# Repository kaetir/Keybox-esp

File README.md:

# Keybox-esp
Nouvelle version de la keybox avec un esp32

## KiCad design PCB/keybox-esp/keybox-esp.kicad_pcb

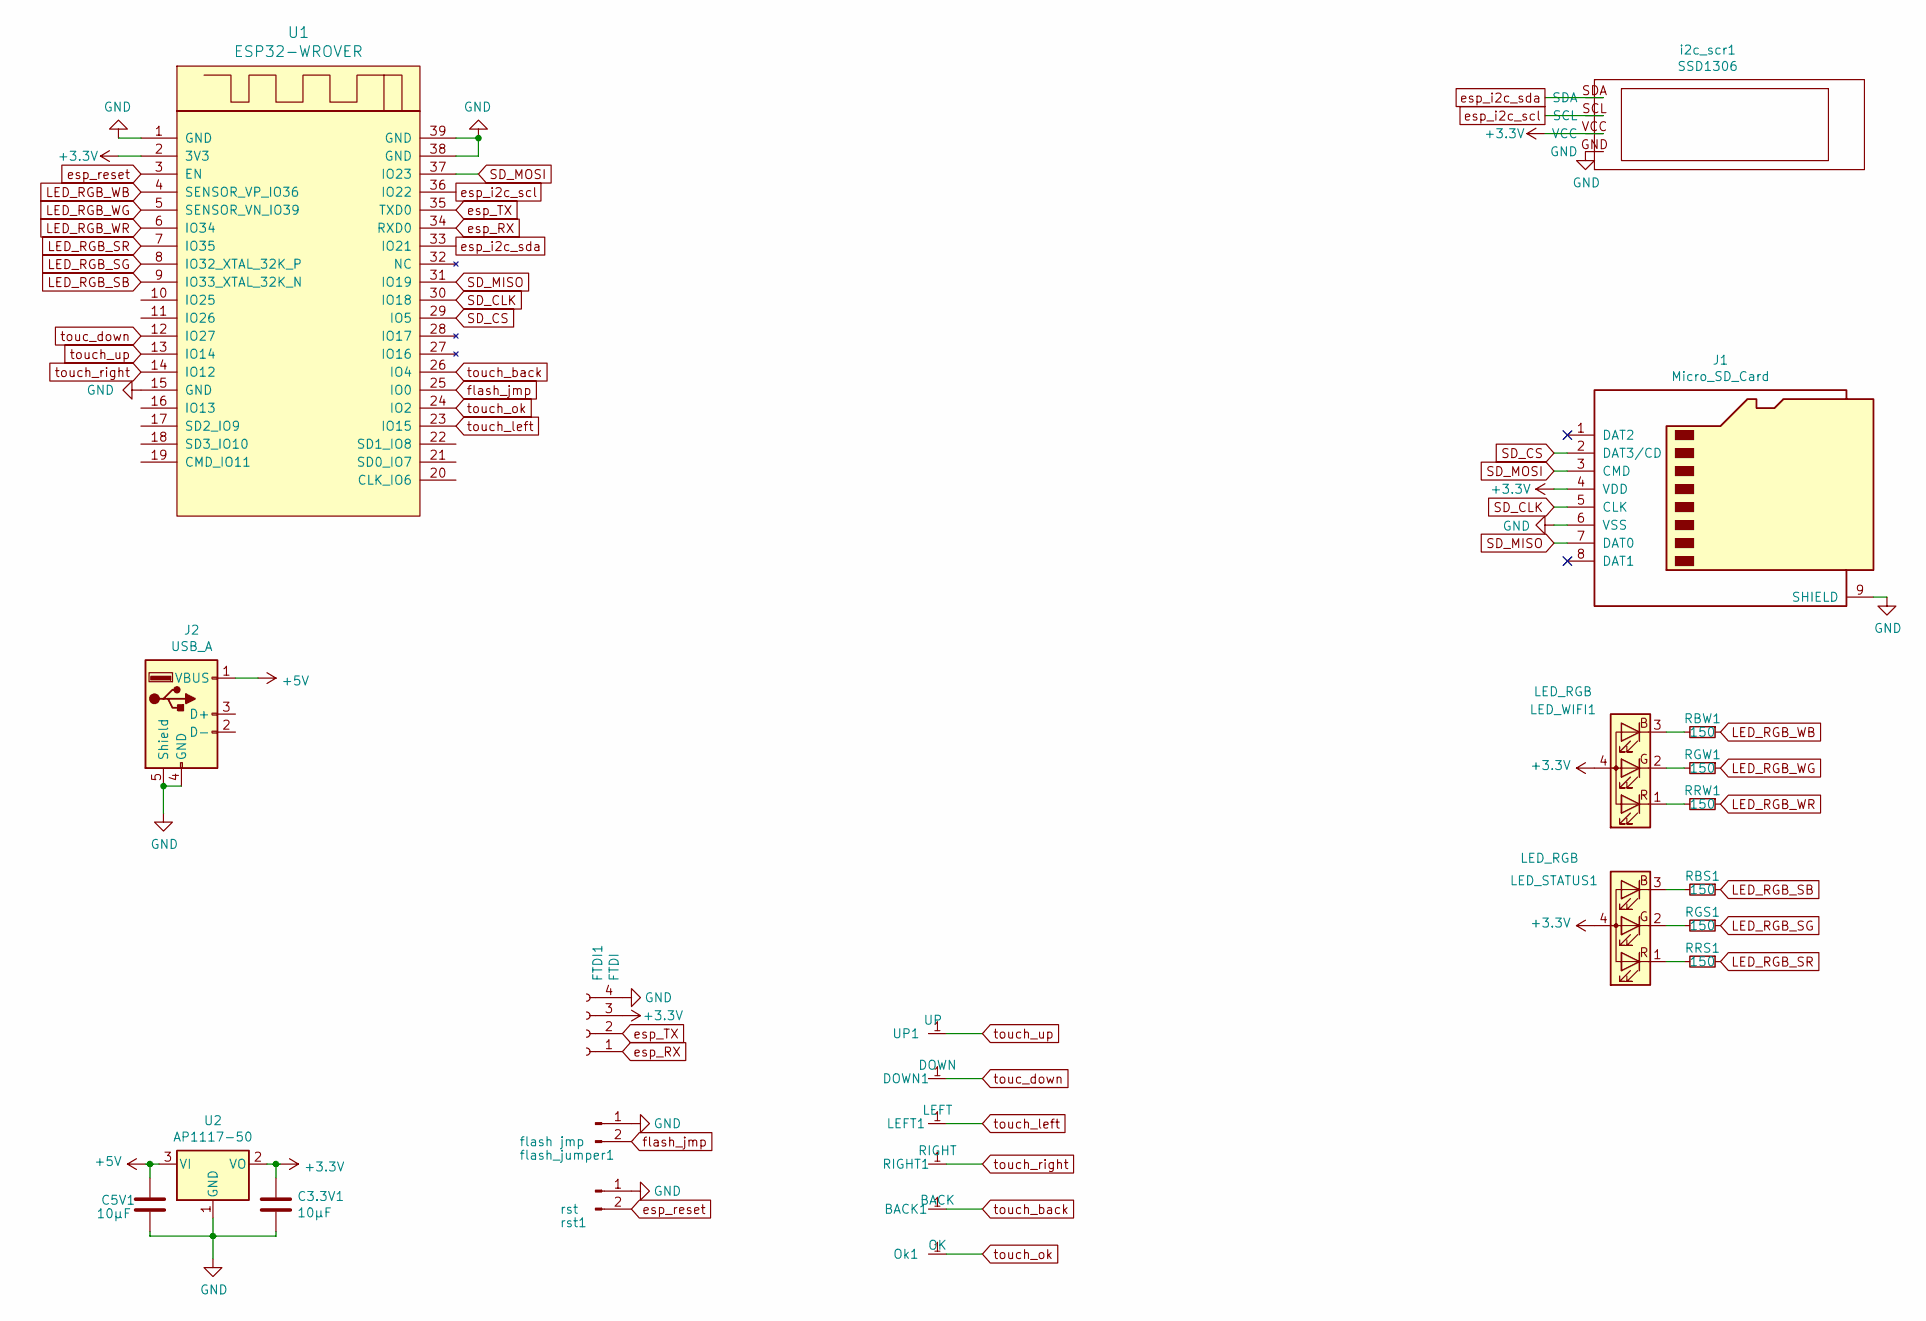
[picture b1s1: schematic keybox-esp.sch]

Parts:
BACK1: BACK; simple_pad_solder
C3.3V1, C5V1: 10µF; C_1206_3216Metric
DOWN1: DOWN; simple_pad_solder
FTDI1: FTDI; SolderWirePad_1x04_P3.175mm_Drill0.8mm
J1: Micro_SD_Card; microSD_HC_Hirose_DM3AT-SF-PEJM5
J2: USB_A; USB3_A_Plug_Wuerth_692112030100_Horizontal
LED_STATUS1: LED_RGB; LED_Avago_PLCC4_3.2x2.8mm_CW
LED_WIFI1: LED_RGB; LED_Avago_PLCC4_3.2x2.8mm_CW
LEFT1: LEFT; simple_pad_solder
Ok1: OK; simple_pad_solder
RBS1: 150; R_1206_3216Metric_Pad1.42x1.75mm_HandSolder
RBW1: 150; R_1206_3216Metric_Pad1.42x1.75mm_HandSolder
RGS1: 150; R_1206_3216Metric_Pad1.42x1.75mm_HandSolder
RGW1: 150; R_1206_3216Metric_Pad1.42x1.75mm_HandSolder
RIGHT1: RIGHT; simple_pad_solder
RRS1: 150; R_1206_3216Metric_Pad1.42x1.75mm_HandSolder
RRW1: 150; R_1206_3216Metric_Pad1.42x1.75mm_HandSolder
U1: ESP32-WROVER
U2: AP1117-50; SOT-223-3Lead_TabPin2
UP1: UP; simple_pad_solder
flash_jumper1: flash jmp; jumper_smd
i2c_scr1: SSD1306; i2c_screen
rst1: rst; jumper_smd

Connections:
+3V3: C3.3V1.1, FTDI1.3, J1.4 (VDD), LED_STATUS1.4 (A), LED_WIFI1.4 (A), U1.2 (3V3), U2.2 (VO), i2c_scr1.VCC; also elsewhere on the board
+5V: C5V1.1, J2.1 (VBUS), U2.3 (VI)
GND: C3.3V1.2, C5V1.2, FTDI1.4, J1.6 (VSS), J1.9 (SHIELD), J2.4 (GND), J2.5 (Shield), U1.1 (GND), U1.15 (GND), U1.38 (GND), U1.39 (GND), U2.1 (GND), flash_jumper1.1, rst1.1
LED_RGB_SB: RBS1.1, U1.9 (IO33_XTAL_32K_N)
LED_RGB_SG: RGS1.1, U1.8 (IO32_XTAL_32K_P)
LED_RGB_SR: RRS1.1, U1.7 (IO35)
LED_RGB_WB: RBW1.1, U1.4 (SENSOR_VP_IO36)
LED_RGB_WG: RGW1.1, U1.5 (SENSOR_VN_IO39)
LED_RGB_WR: RRW1.1, U1.6 (IO34)
unnamed 13: LED_STATUS1.1 (RK), RRS1.2; also elsewhere on the board
unnamed 14: LED_STATUS1.2 (GK), RGS1.2; also elsewhere on the board
unnamed 15: LED_STATUS1.3 (BK), RBS1.2; also elsewhere on the board
unnamed 16: LED_WIFI1.1 (RK), RRW1.2; also elsewhere on the board
unnamed 17: LED_WIFI1.2 (GK), RGW1.2; also elsewhere on the board
unnamed 18: LED_WIFI1.3 (BK), RBW1.2; also elsewhere on the board
SD_CLK: J1.5 (CLK), U1.30 (IO18)
SD_CS: J1.2 (DAT3/CD), U1.29 (IO5)
SD_MISO: J1.7 (DAT0), U1.31 (IO19)
SD_MOSI: J1.3 (CMD), U1.37 (IO23)
esp_RX: FTDI1.1, U1.34 (RXD0)
esp_TX: FTDI1.2, U1.35 (TXD0)
esp_i2c_scl: U1.36 (IO22), i2c_scr1.SCL
esp_i2c_sda: U1.33 (IO21), i2c_scr1.SDA
esp_reset: U1.3 (EN), rst1.2
flash_jmp: U1.25 (IO0), flash_jumper1.2
touc_down: DOWN1.1, U1.12 (IO27)
touch_back: BACK1.1, U1.26 (IO4)
touch_left: LEFT1.1, U1.23 (IO15)
touch_ok: Ok1.1, U1.24 (IO2)
touch_right: RIGHT1.1, U1.14 (IO12)
touch_up: U1.13 (IO14), UP1.1

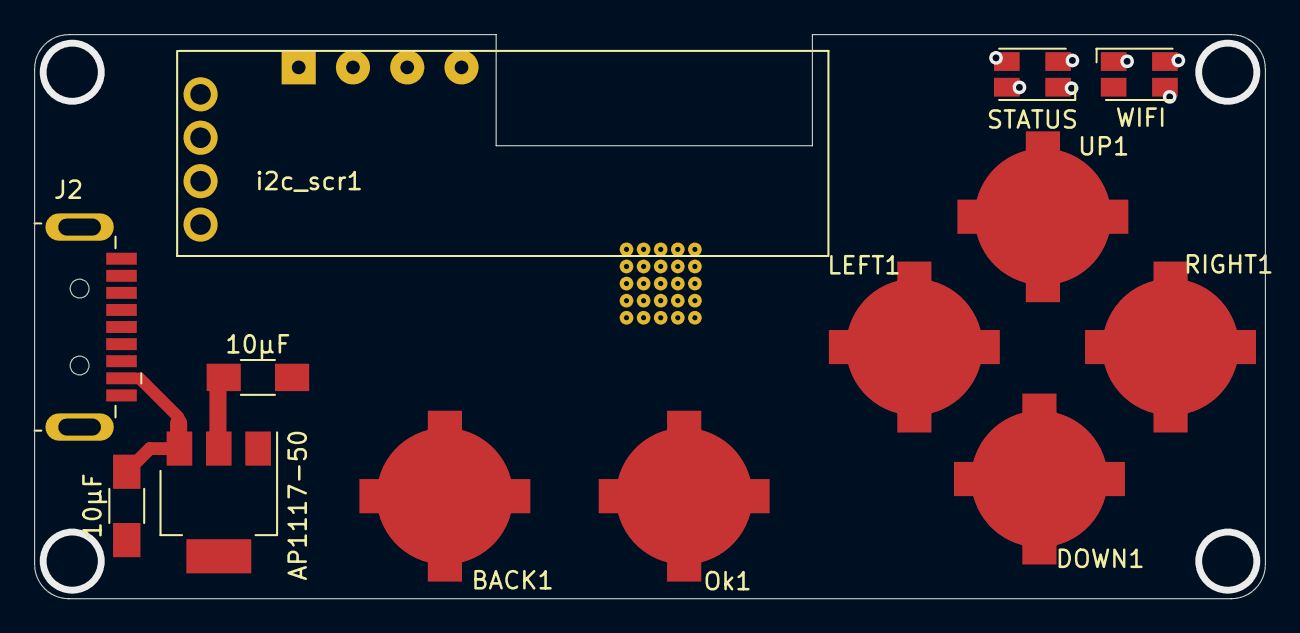
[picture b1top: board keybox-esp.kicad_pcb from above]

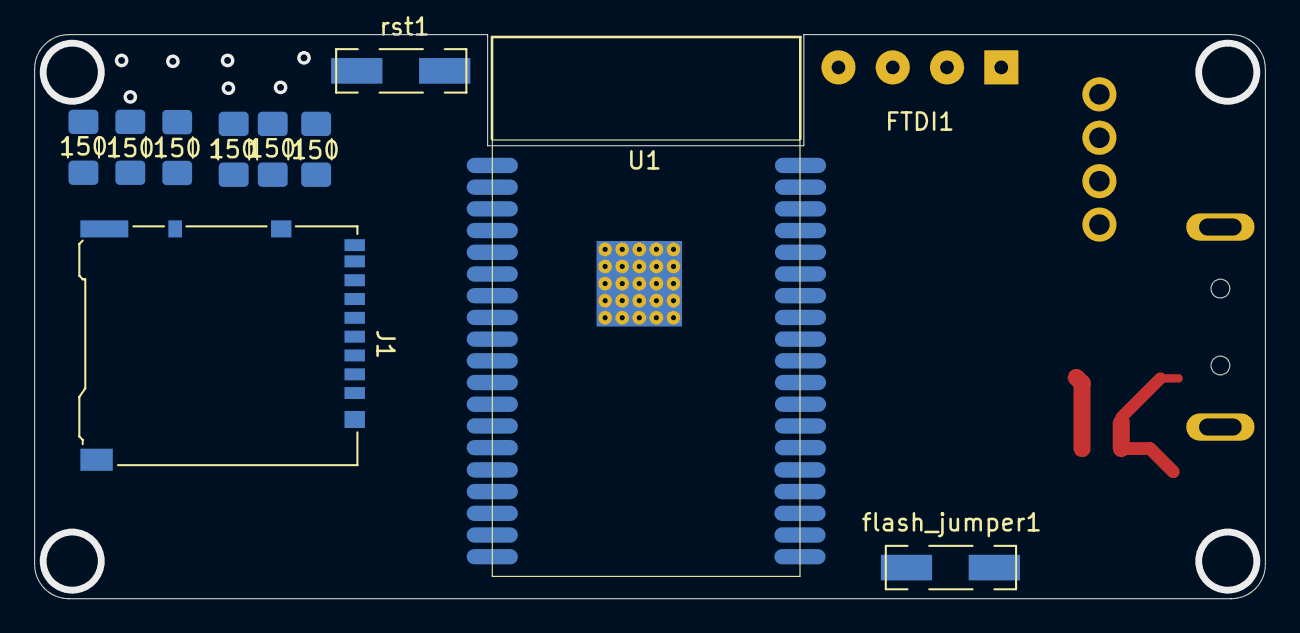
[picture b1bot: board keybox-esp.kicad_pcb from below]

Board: 2 copper layers, 72.0 x 33.0 mm, 24 parts (11 on the bottom side), 31 nets.

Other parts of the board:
STATUS: LED_RGB; LED_Avago_PLCC4_3.2x2.8mm_CW
WIFI: LED_RGB; LED_Avago_PLCC4_3.2x2.8mm_CW

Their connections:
+3V3: STATUS.4, WIFI.4; also elsewhere on the board
unnamed 13: STATUS.1; also elsewhere on the board
unnamed 14: STATUS.2; also elsewhere on the board
unnamed 15: STATUS.3; also elsewhere on the board
unnamed 16: WIFI.1; also elsewhere on the board
unnamed 17: WIFI.2; also elsewhere on the board
unnamed 18: WIFI.3; also elsewhere on the board

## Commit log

2020-03-16 Ajout du test écran
2020-03-16 ajout sd card test
2020-03-17 ajout graph foncitonnement wallet
2020-03-18 Ajout du fritzing et du shemat des pins
2020-03-18 ajout du gitignore
2020-03-18 ajout des composant principaux du pcb
2020-03-18 Ajout de la partie interface du systeme
2020-03-19 Ajout du dossier de langue des menu
2020-03-19 Ajout de code pour la classe Display
2020-03-19 main.cpp
2020-03-19 Modifi du comportement du loop dans main et ajout de code dans buttons
2020-03-20 Modifying interface class structure
2020-03-20 ajout de login() et de typing_input()
2020-03-23 modifs de la classe View et ajout des test unitaire de celle-ci
2020-03-23 Adding a capacitive touch tester
2020-03-23 PCB sans wireing ni usb
2020-03-23 ajout du ftdi
2020-03-24 deleting a useless variable and moving the filenames
2020-03-24 Adding has_input() in Controller
2020-03-24 Testing has_input() and get_input() in Controller
2020-03-24 implementing the read() function in the Model
2020-03-24 adding of menu_dispay and update_display() in Controller
2020-03-24 Comments on Controller and View
2020-03-24 Test of class combination
2020-03-26 Adding Scroll() in Controller
2020-03-26 Adding comments
2020-03-26 modifying Webserver menu layout
2020-03-26 Modifying menus layout
2020-03-26 Modif /LANG/FR
2020-03-27 Modif folder structure
2020-03-27 Adding menu structures files
2020-03-27 Adding load_menu() in Controller
2020-03-30 Add files via upload
    web part
2020-03-30 adding encrypt/decrypt func
2020-03-30 little mistake
2020-03-30 ajout test SPIFFS
2020-03-31 ajout de Screen, modifs de la fonction read() et load_menu()
2020-03-31 a little bit cleaner code
2020-03-31 ajout de leds RGB
2020-04-01 Ajout de la sous classe Inputs
2020-04-01 Ajout de commentaire dans Controller.h
2020-04-01 Plus de commentaire
2020-04-01 Ajout de Commentaires dans /STRUCTURE/README/md
2020-04-01 AJout commentaire dans Inputs
2020-04-01 Commentaires View
2020-04-01 Ajout de go_back() et select_choice()
2020-04-07 Ajout du test des menu/input fields
2020-04-07 Ajout de la partie graphique
2020-04-08 Rajout de commentaire et du Keyboard
2020-04-08 Adding data/ Folder
2020-04-08 Deleting Menu/ Folder in src/
2020-04-08 Ajout de Serial print commandés par le DEBUG_MODE
2020-04-08 renomage partie web
2020-04-08 ajout du projet platformio pour le server web
2020-04-08 Modif pcb non push
    oupsi
2020-04-08 Update index.htm
    prob avec la navbar
2020-04-08 Auto stash before merge of "master" and "origin/master"
2020-04-10 Modification du nom de WIDTH en FIELD_WIDTH
2020-04-10 Ajout d'une option pour choisir une langue
2020-04-10 Correction
2020-04-12 Web server exemple
2020-04-12 modif du gitignore pour le fichier de créditential
2020-04-13 Update du dossier data
2020-04-13 Ajout des tests unitaires
2020-04-13 Ajout d'un dossier de documentation
2020-04-13 README.md
2020-04-13 README
2020-04-13 images readme
2020-04-13 images
2020-04-13 Test image
2020-04-13 Test image 2
2020-04-13 AJout image
2020-04-13 modification du web server de base pour un simple
2020-04-13 Serveur web https avec certificat autosigné donc a valider
    certificat pour test uniquement
2020-04-13 web serveur HTTPS SPIFFS fonctionnel
2020-04-14 Ajout de commentaires au format doxygen
2020-04-14 AJout de log
2020-04-14 Test Wifi esp32
    test wifi
2020-04-14 modif ligne inutile
2020-04-14 SPIFFS_tools pour plus de plaisir
2020-04-14 pour VSCODE
2020-04-14 https server, Marche pas encore
    Problem de task
2020-04-14 Suppression de log.txt
2020-04-14 Ajout des nouveau menu
2020-04-15 Add wallet and account class
2020-04-15 a little mistake
2020-04-15 AJout de code dans Model et dans Controller
2020-04-15 Ajout de send_ids()
2020-04-15 boolean hotspot in Model
2020-04-15 STRUCTURE.md
2020-04-15 Errors still to be determined
    some advancement but huge bug to be resolved
2020-04-16 Correction de l'affichage du curseur à son initialisation
2020-04-16 MENU.md
2020-04-16 CLASS.md
2020-04-17 Still some bugs in progress
    some bugs I know where they are i am working on them
2020-04-19 almost finished
    * miss 2 functions asked by antonoir
    * to do commentary and more readable code
2020-04-20 all functions asked usable
    still miss some clarity in the code
2020-04-20 WiFi functions added - not working
2020-04-20 https server fonctionnel
2020-04-20 Structure intégration
2020-04-20 a little modif
2020-04-20 patch_wifi
2020-04-20 For integration
2020-04-20 integration wifi client + server marche
2020-04-21 Crypto add JSON
2020-04-21 Integration interface & crypto
2020-04-21 Integration Interface web server wifi
2020-04-21 Ajout de modif web_server
2020-04-21 Web_server
2020-04-22 supression d'un lien innutile
2020-04-22 Update doc
2020-04-22 Debug and comments
2020-04-22 a tiny mistake
    remove an include
2020-04-22 integration finale marche presque
2020-04-23 partie web update pour le server
2020-04-23 Creation du wallet qui marche
2020-04-23 Test integration Crypto + Web
2020-04-24 Integration bug update
2020-04-24 Update: Scroll and Cursor
2020-04-24 Update Wifi list and Account list
2020-04-24 Add Wifi cache
2020-04-24 Modif name
2020-04-24 Comment
2020-04-24 Update: doc
2020-04-24 update web
    need fix on submit add form
2020-04-24 Supression de la page login qui est inutile du fait que l'auth se fait sur l'esp
2020-04-24 a little commentary modification
2020-04-24 Add special chars
2020-04-24 ajout du doxyfile et du readme de doc
2020-04-24 clang-format
2020-04-27 update js
2020-04-27 patch js
2020-04-27 modif wifi key
2020-04-27 Serveur web qui marche bien
2020-04-27 path en relatif
2020-04-27 Modif content & Wifi keys
2020-04-27 server was not starting
2020-04-27 Final changes
2020-04-27 Lib adafruit modifié pour logo
2020-04-27 cleaning the imports
2020-04-28 update doc doxygen
2020-04-29 Ajout doc img (mermaid)
